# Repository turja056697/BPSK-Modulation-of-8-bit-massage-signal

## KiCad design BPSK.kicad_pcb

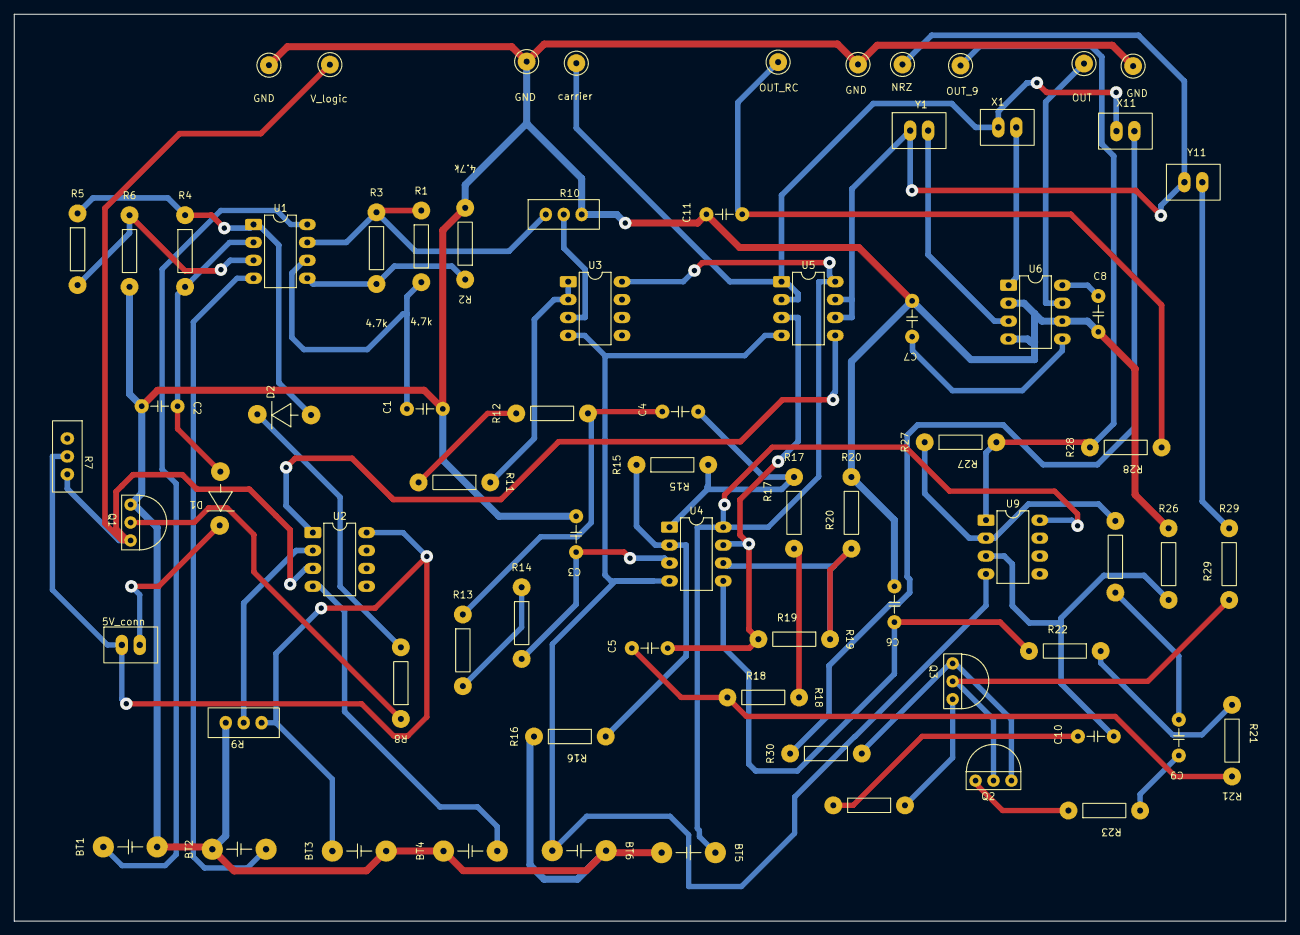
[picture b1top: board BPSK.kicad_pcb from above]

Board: 2 copper layers, 180.2 x 128.5 mm, 74 parts (0 on the bottom side), 53 nets.

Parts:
5V_conn: TWO_POST_CONN; 2_post_conn
BT1, BT2, BT3, BT4, BT5, BT6: Battery
C1, C3, C4, C5, C6: 10nF; Capacitor
C2: 1uF; Capacitor
C7, C8: 0.1uF; Capacitor
C9, C10, C11: 4.7nF; Capacitor
D1, D2: diode
GND: 4_male_header
GND#2, GND#3, GND#4: 4_male_header
NRZ: 4_male_header
OUT: 4_male_header
OUT_9: 4_male_header
OUT_RC: 4_male_header
Q1, Q2: Q_NPN_BEC; bjt
Q3: Q_PNP_BCE; bjt
R1, R2, R3: 4.7k; Resistor
R4, R30: 10k; Resistor
R5, R6, R8, R16, R20: 10K; Resistor
R7, R9, R10: trimmer_pot
R11, R13, R15, R17, R21: 1.5k; Resistor
R12, R14, R18, R22, R23, R24: 100; Resistor
R19: 12k; Resistor
R25, R26, R27, R29: 15k; Resistor
R28: 1k; Resistor
U1, U3, U4, U5: TL072; DIP-8_W7.62mm_LongPads
U2: TLC2272; DIP-8_W7.62mm_LongPads
U6: AD633; DIP-8_W7.62mm_LongPads
U9: NE5532; DIP-8_W7.62mm_LongPads
V_logic: 4_male_header
X1, X11: TWO_POST_CONN; 2_post_conn
Y1, Y11: TWO_POST_CONN; 2_post_conn
carrier: 4_male_header

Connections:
/1IN+: R5.2, R6.1, U1.3 (1IN+)
/1IN-: C2.1, D1.1 (A), R4.2, U1.2 (1IN-)
/1out: D2.1 (A), R4.1, R5.1, U1.1 (1OUT)
/2IN+: R2.1, R3.2, U1.5 (2IN+)
/2IN-: C1.1, R1.2, U1.6 (2IN-)
/+5V: 5V_conn.1 (CON1), BT3.1 (+), R7.2, R9.1, U2.8 (VCC)
/+9V: BT1.1 (+), U1.8 (VCC)
/+15V: BT5.1 (+), U3.8 (VCC), U4.8 (VCC), U5.8 (VCC), U9.8 (VCC)
/+IN_9: C10.2, R26.2, U9.3 (1IN+)
/-5V: BT4.2 (-), U2.4 (VEE)
/-9V: BT2.2 (-), U1.4 (VEE)
/-15V: BT6.2 (-), U3.4 (VEE), U4.4 (VEE), U5.4 (VEE), U9.4 (VEE)
/-IN_9: R25.2, R27.1, U9.2 (1IN-)
/BIPOLAR: U2.1 (1OUT), U5.5 (2IN+)
/NRZ: NRZ.1 (H), U5.6 (2IN-), U5.7 (2OUT), Y1.1 (CON1), Y11.1 (CON1)
/OUT: OUT.1 (H), U6.7 (W)
/OUT_2: C11.2, OUT_RC.1 (H), R28.2
/OUT_9: OUT_9.1 (H), R27.2, R28.1, U9.1 (1OUT)
/S_1IN+: C3.1, R14.2, U4.3 (1IN+)
/S_1IN-: R15.1, R16.2, U4.2 (1IN-)
/S_1OUT: C4.2, R15.2, R17.1, U4.1 (1OUT)
/S_2IN+: C6.1, R22.2, U4.5 (2IN+)
/S_2IN-: R19.1, R20.2, U4.6 (2IN-)
/S_2OUT: C5.2, R19.2, U4.7 (2OUT), U5.3 (1IN+)
/U2_IN-: R9.2, U2.2 (1IN-)
/U3_IN+: R10.2, U3.3 (1IN+)
/V_logic: Q1.3 (C), R7.3, U2.3 (1IN+), V_logic.1 (H)
/V_sqr: R1.1, R3.1, R10.1, U1.7 (2OUT)
/X1: U6.1 (X1), X1.2 (CON2)
/X11: R30.1, X11.2 (CON2)
/Y1: U6.3 (Y1), Y1.2 (CON2)
/Y11: R29.1, Y11.2 (CON2)
/carrier: U5.1 (1OUT), U5.2 (1IN-), X1.1 (CON1), X11.1 (CON1), carrier.1 (H)
/fill_in: R11.1, U3.1 (1OUT), U3.2 (1IN-)
GND: BT1.2 (-), BT2.1 (+), BT3.2 (-), BT4.1 (+), BT5.2 (-), BT6.1 (+), C1.2, C2.2, C3.2, C6.2, C7.2, C8.2, C11.1, GND.1 (H), GND#2.1 (H), GND#3.1 (H), GND#4.1 (H), Q1.1 (E), R2.2, R6.2, R9.3, R10.3, R16.1, R20.1, R26.1, U6.2 (X2), U6.4 (Y2), U6.6 (Z)
unnamed: C4.1, R12.2, R13.1
unnamed: C5.1, R18.2, R21.1
unnamed: C9.1, R23.2
unnamed: C9.2, R25.1
unnamed: C10.1, R24.2
unnamed: 5V_conn.2 (CON2), D1.2 (C)
unnamed: D2.2 (C), R8.2
unnamed: Q1.2 (B), R8.1
unnamed: Q2.2 (B), Q3.2 (B), R29.2
unnamed: Q2.3 (C), Q3.1 (E), R30.2
unnamed: Q2.1 (E), R23.1
unnamed: Q3.3 (C), R24.1
unnamed: R11.2, R12.1
unnamed: R13.2, R14.1
unnamed: R17.2, R18.1
unnamed: R21.2, R22.1
unnamed: C8.1, U6.8 (VS+)
unnamed: C7.1, U6.5 (VS-)
